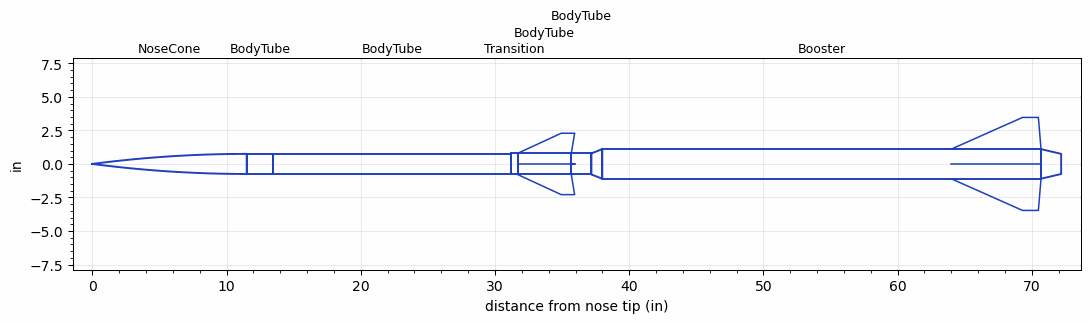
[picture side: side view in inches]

<RASAeroDocument>
 <FileVersion>2</FileVersion>
 <RocketDesign>
  <NoseCone>
   <Length>11.5</Length>
   <Diameter>1.4961</Diameter>
   <Shape>Tangent Ogive</Shape>
   <BluntRadius>0.065</BluntRadius>
   <Location>0</Location>
  </NoseCone>
  <BodyTube>
   <Length>1.968504</Length>
   <Diameter>1.4961</Diameter>
   <Location>11.5</Location>
  </BodyTube>
  <BodyTube>
   <Length>17.71654</Length>
   <Diameter>1.4961</Diameter>
   <Location>13.4685</Location>
  </BodyTube>
  <Transition>
   <Length>0.5</Length>
   <Diameter>1.575</Diameter>
   <Location>31.18504</Location>
   <RearDiameter>1.575</RearDiameter>
  </Transition>
  <BodyTube>
   <Length>4</Length>
   <Diameter>1.575</Diameter>
   <Location>31.68504</Location>
   <Fin>
    <Count>4</Count>
    <Chord>4</Chord>
    <Span>1.5</Span>
    <SweepDistance>3.25</SweepDistance>
    <TipChord>1</TipChord>
    <Thickness>0.075</Thickness>
    <LERadius>0.065</LERadius>
    <Location>4</Location>
    <AirfoilSection>Hexagonal</AirfoilSection>
    <FX1>0.25</FX1>
    <FX3>0.25</FX3>
   </Fin>
  </BodyTube>
  <BodyTube>
   <Length>1.5</Length>
   <Diameter>1.575</Diameter>
   <Location>35.68504</Location>
  </BodyTube>
  <Booster>
   <Length>32.6929</Length>
   <Diameter>2.2047</Diameter>
   <InsideDiameter>1.575</InsideDiameter>
   <RailGuideDiameter>0.373</RailGuideDiameter>
   <RailGuideHeight>0.3</RailGuideHeight>
   <Location>37.18504</Location>
   <ShoulderLength>0.809</ShoulderLength>
   <BoattailLength>1.5</BoattailLength>
   <BoattailRearDiameter>1.5</BoattailRearDiameter>
   <Fin>
    <Count>4</Count>
    <Chord>6.6929</Chord>
    <Span>2.3622</Span>
    <SweepDistance>5.315</SweepDistance>
    <TipChord>1.1811</TipChord>
    <Thickness>0.1575</Thickness>
    <LERadius>0.05</LERadius>
    <Location>6.6929</Location>
    <AirfoilSection>Hexagonal</AirfoilSection>
    <FX1>0.5</FX1>
    <FX3>0.5</FX3>
   </Fin>
  </Booster>
  <Surface>Camouflage Paint</Surface>
  <ModifiedBarrowman>True</ModifiedBarrowman>
  <Turbulence>True</Turbulence>
  <UseBooster1>False</UseBooster1>
  <UseBooster2>False</UseBooster2>
 </RocketDesign>
 <LaunchSite>
  <Altitude>2000</Altitude>
  <Pressure>29.9</Pressure>
  <RodAngle>1</RodAngle>
  <RodLength>10</RodLength>
  <Temperature>74</Temperature>
  <WindSpeed>10</WindSpeed>
 </LaunchSite>
 <Recovery>
  <Altitude1>1000</Altitude1>
  <Altitude2>1000</Altitude2>
  <DeviceType1>None</DeviceType1>
  <DeviceType2>None</DeviceType2>
  <Event1>False</Event1>
  <Event2>False</Event2>
  <Size1>1</Size1>
  <Size2>1</Size2>
  <EventType1>None</EventType1>
  <EventType2>None</EventType2>
  <CD1>1.33</CD1>
  <CD2>1.33</CD2>
 </Recovery>
 <SimulationList>
  <Simulation>
   <SustainerEngine>J360  (Walter)</SustainerEngine>
   <SustainerLaunchWt>3.57</SustainerLaunchWt>
   <SustainerNozzleDiameter>1.25</SustainerNozzleDiameter>
   <SustainerCG>21.56</SustainerCG>
   <SustainerIgnitionDelay>10.5</SustainerIgnitionDelay>
   <Booster1Engine>L898  (thomas)</Booster1Engine>
   <Booster1LaunchWt>10.25</Booster1LaunchWt>
   <Booster1SeparationDelay>0</Booster1SeparationDelay>
   <Booster1IgnitionDelay>0</Booster1IgnitionDelay>
   <Booster1CG>44.5</Booster1CG>
   <Booster1NozzleDiameter>1.25</Booster1NozzleDiameter>
   <IncludeBooster1>True</IncludeBooster1>
   <Booster2Delay>0</Booster2Delay>
   <IncludeBooster2>False</IncludeBooster2>
   <TimetoApogee>63.65591</TimetoApogee>
   <MaxAltitude>68938.38</MaxAltitude>
   <MaxVelocity>3087.711</MaxVelocity>
   <OptimumWt>3.57</OptimumWt>
   <OptimumMaxAlt>3.57</OptimumMaxAlt>
  </Simulation>
 </SimulationList>
</RASAeroDocument>
